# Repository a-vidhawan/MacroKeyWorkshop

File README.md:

# MacroKeyWorkshop
Repository with all required files and instructions for the Macro Key Workshop - first held in Spring 2025.

## Navigation
- [First Steps](#first-steps)
- [Installing the Configuration Software](#installing-the-configuration-software)
  - [MacOS](#macos)
  - [Windows](#windows)
- [Using the Software](#using-the-software)
  - [Configuring Keys](#configuring-keys)
- [Workshop Activity](#workshop-activity)

## First Steps:
- Open Arduino IDE on your computer.
- Snap the Mini keyboard onto the Arduino.
- Plug the Arduino into your computer.
- Download the `.ino` for the workshop from the Arduino INOs folder.
- Upload (->) the firmware to your Arduino. Make sure there are no errors.
- Open Serial Monitor (Tools -> Serial Monitor) and test the controls on the device to check if you are receiving data.

## Installing the Configuration Software:
### MacOS:

- On GitHub, click on the zip file that corresponds to your MacOS version (`MacroPad-MacOS-10_XX.zip`).
- On the right of the screen, click on the "Download raw file" button.
- Unzip the downloaded file, and double click the `MacroPad.app` that appears. MacOS will likely not allow you to open the app yet.
- Go to your Mac settings app, and go to Privacy and Security and scroll all the way down. Next to the message that says that `MacroPad.app` was blocked, click "Open Anyway."

### Windows:

- Click on `Tags` on the home page, and head over to the `v1.0.0-alpha-2` release.
- Download the zip file.
- Extract, and then just double-click on `MacroPad.exe`

## Using the Software
### Configuring Keys:
- In the Software, click on the key you want to assign the function to.
- Select a **combination of keys** (Doesn't currently work on Mac) OR 
- Select an **executable** to assign.
- Click `Save`.
- Your keys should now do what you've selected them to.
- The knob is restricted to volume for this workshop. Pressing the knob mutes audio.

## Workshop Activity:
- FIll in the blanks in the `MacroKeyWorkshop.ino` file, by looking at the `mainwindow.cpp` file.
- You can find `mainwindow.cpp` in the software folder in the repo.
- After filling the blanks, you can upload the code to the Arduino without errors. You're now all set to use the configuration software.

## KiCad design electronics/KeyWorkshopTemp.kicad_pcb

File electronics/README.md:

These are the schematic and pcb files. Designed in KiCAD

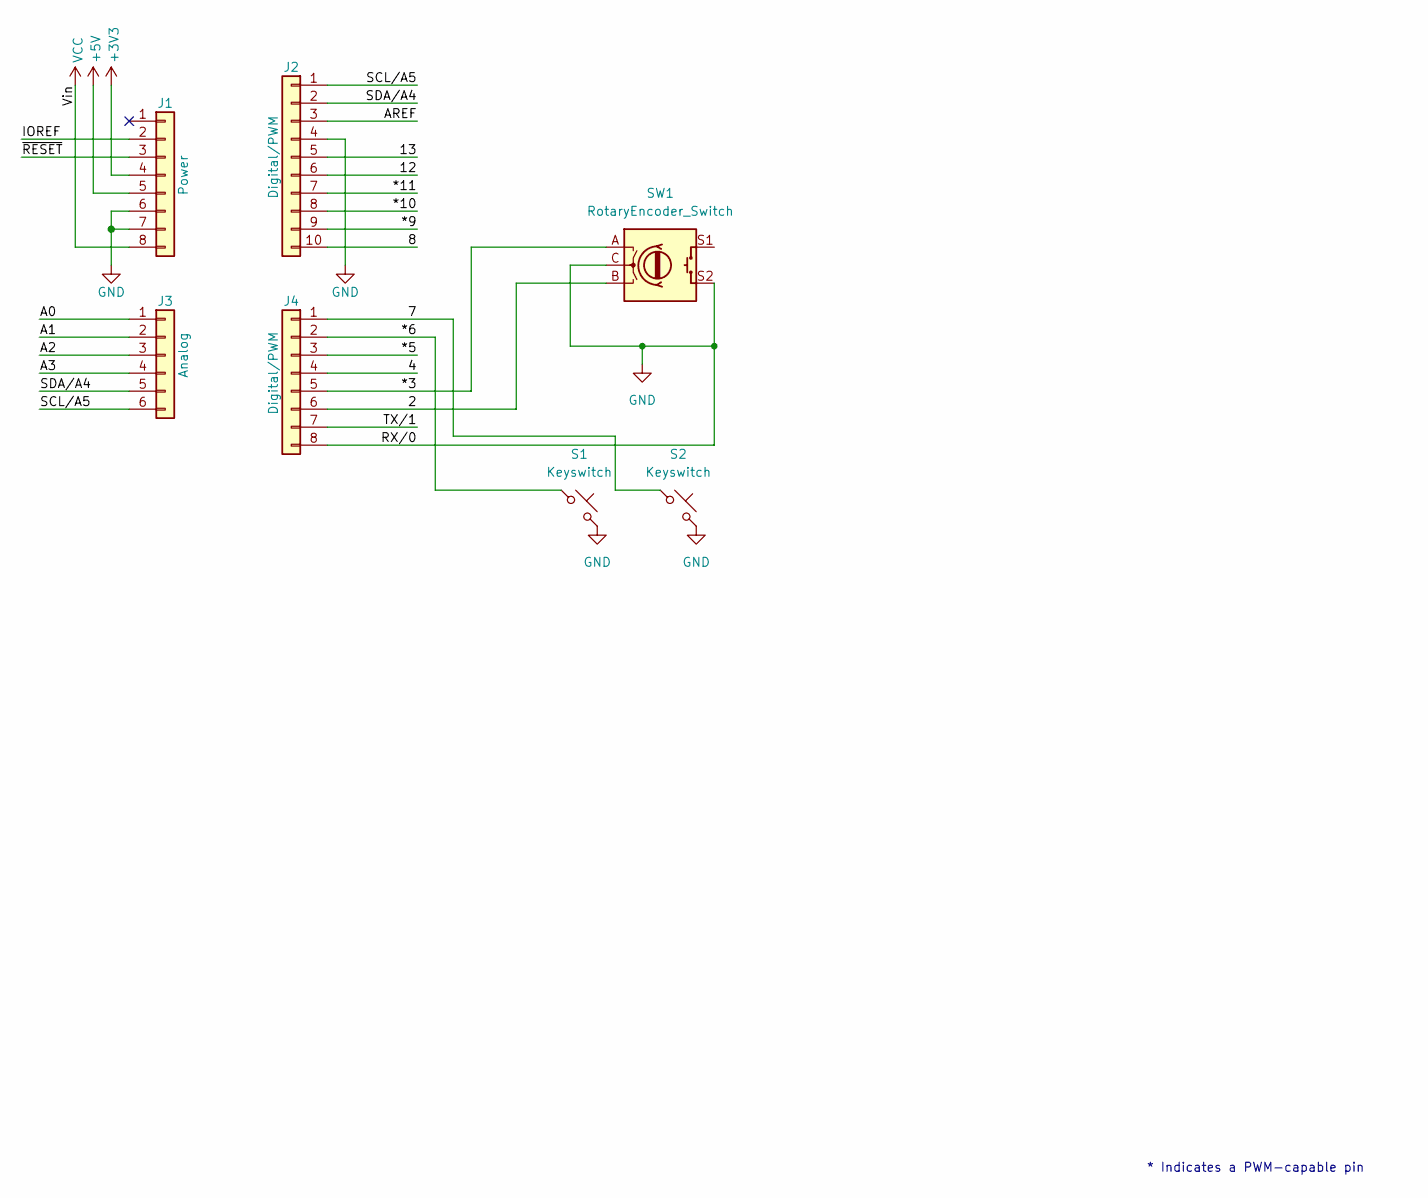
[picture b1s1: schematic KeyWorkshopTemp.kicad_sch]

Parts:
J1: Power; PinSocket_1x08_P2.54mm_Vertical
J2: Digital/PWM; PinSocket_1x10_P2.54mm_Vertical
J3: Analog; PinSocket_1x06_P2.54mm_Vertical
J4: Digital/PWM; PinSocket_1x08_P2.54mm_Vertical
S1, S2: Keyswitch; MX_PCB_1.00u
SW1: RotaryEncoder_Switch; RotaryEncoder_Alps_EC11E-Switch_Vertical_H20mm

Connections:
+3V3: J1.4
+5V: J1.5
/2: J4.6, SW1.B
/4: J4.4
/7: J4.1, S2.1
/8: J2.10
/12: J2.6
/13: J2.5
/*3: J4.5, SW1.A
/*5: J4.3
/*6: J4.2, S1.1
/*9: J2.9
/*10: J2.8
/*11: J2.7
/A0: J3.1
/A1: J3.2
/A2: J3.3
/A3: J3.4
/AREF: J2.3
/IOREF: J1.2
/SCL/A5: J2.1, J3.6
/SDA/A4: J2.2, J3.5
/TX/1: J4.7
/~RESET: J1.3
VCC: J1.8

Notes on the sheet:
* Indicates a PWM-capable pin

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
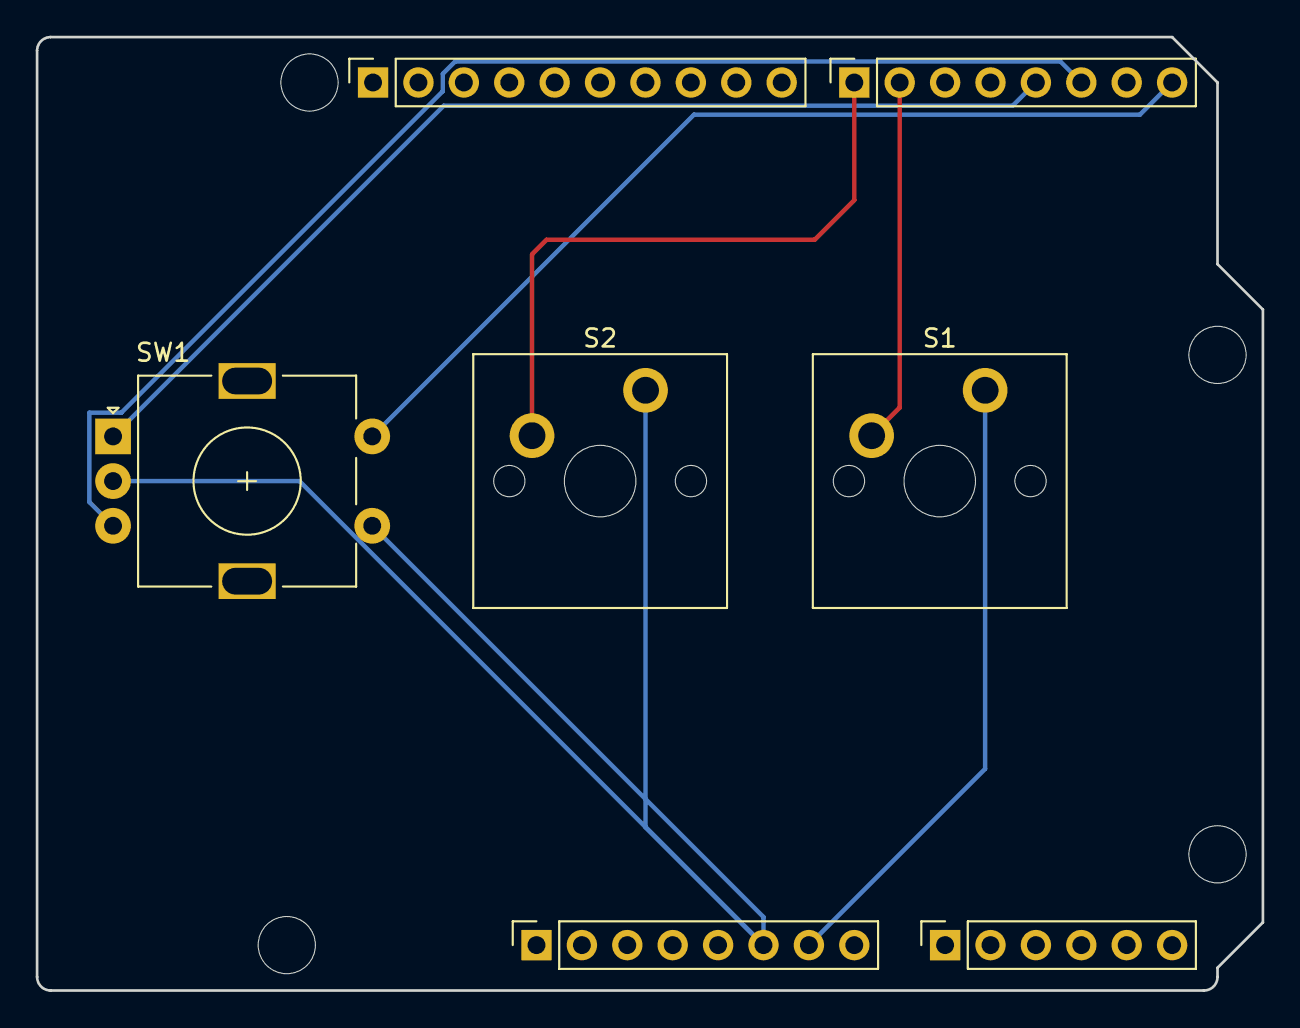
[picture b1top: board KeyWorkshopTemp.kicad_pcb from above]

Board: 2 copper layers, 68.6 x 53.3 mm, 11 parts (0 on the bottom side), 8 nets.

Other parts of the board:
MH1, MH2, MH3, MH4: MountingHole_3.2mm

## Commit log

2025-04-12 Initial commit
    FIrst
2025-04-13 Initial software commit
2025-04-13 Serial handler added?
    Inital
2025-04-13 Resolved conflicts
2025-04-13 2
    2
2025-04-13 3
    3
2025-04-16 Got two keys and volume working on mac
2025-04-16 Modified CMakeLists to make Obj-C++ files Mac-exclusive
2025-04-18 Added MacroPad executable for Mac
2025-04-18 Windcows exe added to top level
2025-04-18 Fixed minimum mac version issue?
2025-04-18 deleted exe
2025-04-18 moved build and edited gitignore
2025-04-18 Rebuilt app with macos requirement fixed??
2025-04-18 Fixed mac version thing?
2025-04-18 ignbores
2025-04-18 deleted build
2025-04-19 Profile saving works on Mac
2025-04-19 Fixed CMakeLists
2025-04-20 Implemented executeHotkey for win
    Implemented executeHotkey for windows, and changed onData Received to use executeHotkey
2025-04-20 Fixed executable path macro
    subbed '/' for '\\' since that is correct for Win file hierarchy.
2025-04-20 added zip
2025-04-20 fixed zip
2025-04-20 Added Scroll functions
2025-04-20 Commented out scroll code for now
2025-04-20 Removed some unused imports
2025-04-20 Added windows keystroke code
2025-04-20 Added release version MacroPad.app for mac
2025-04-20 Functionality sorted on "Debug"
2025-04-20 Deployed MacroPad app with libraries inside for mac
2025-04-20 New strat for mac app?
2025-04-20 Added macOS 10.14 build
2025-04-21 Updated README for MacOS instructions
2025-04-21 Added a minimum mac version to CMakeLists
2025-04-21 Update zips
2025-04-21 Rename MacroKeyWorkshop-v1.0.0-alpha-4.zip to MacroKeyWorkshop-v1.0.0-win64-alpha-4.zip
2025-05-14 image Transfer protocol
    Implemented esp32 side image receiver file and qt side image transmitter side.
2025-05-14 updated serial handler code -- needs testing
